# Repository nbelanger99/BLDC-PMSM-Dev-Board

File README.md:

### BLDC/PMSM Dev Board

This board wad designed to prototype control algorithms for BLDC/PMSM type motors. It features the typical 3-phase half-bridge architecture with discrete N-Channel Mosfets, and shunt resistors on two of the phases. It operates at an Arduino/RPi friendly 3.3v logic and breaks all signals out to a 0.1 inch header

With an Arduino or other platform, a battery/power supply, and a motor, this design could be used to start protoyping traditional 6-step commutation, or something more advanced like Field Oriented Control

<br>

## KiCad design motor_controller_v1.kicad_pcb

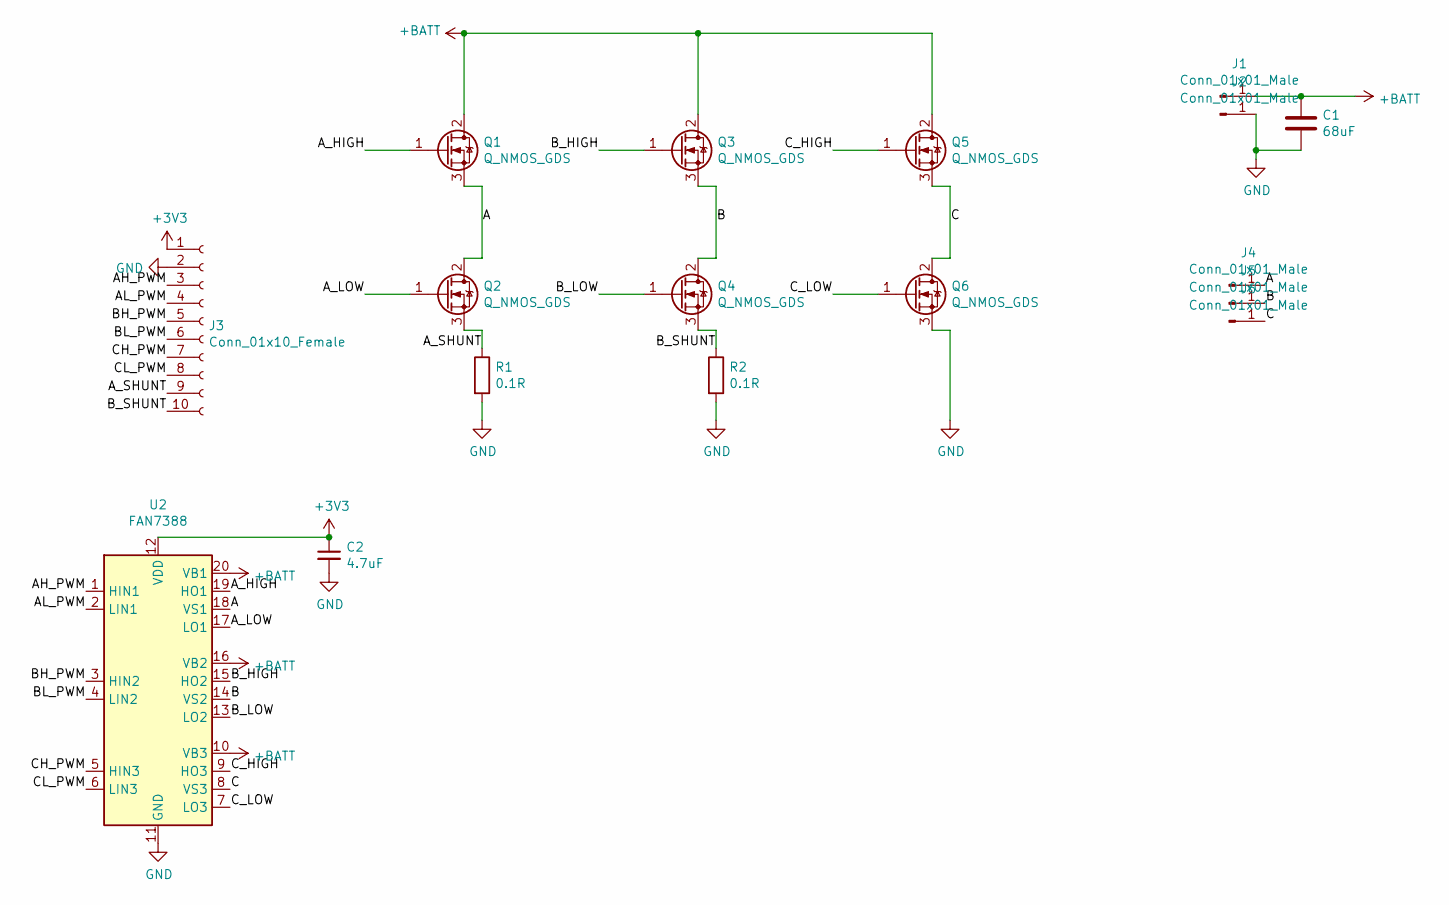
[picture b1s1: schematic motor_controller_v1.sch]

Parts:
C1: 68uF; CP_Radial_D18.0mm_P7.50mm
C2: 4.7uF; C_0603_1608Metric_Pad1.05x0.95mm_HandSolder
J1, J2, J4, J5, J6: Conn_01x01_Male; SolderWirePad_1x01_SMD_5x10mm
J3: Conn_01x10_Female; PinHeader_1x10_P2.54mm_Vertical
Q1, Q2, Q3, Q4, Q5, Q6: Q_NMOS_GDS; TO-220-3_Vertical
R1, R2: 0.1R; R_2512_6332Metric_Pad1.52x3.35mm_HandSolder
U2: FAN7388; SOIC-20W_7.5x12.8mm_P1.27mm

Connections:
+3V3: C2.1, J3.1, U2.12 (VDD)
+BATT: C1.1, J1.1, Q1.2 (D), Q3.2 (D), Q5.2 (D), U2.10 (VB3), U2.16 (VB2), U2.20 (VB1)
/A: J4.1, Q1.3 (S), Q2.2 (D), U2.18 (VS1)
/AH_PWM: J3.3, U2.1 (HIN1)
/AL_PWM: J3.4, U2.2 (LIN1)
/A_HIGH: Q1.1 (G), U2.19 (HO1)
/A_LOW: Q2.1 (G), U2.17 (LO1)
/A_SHUNT: J3.9, Q2.3 (S), R1.1
/B: J5.1, Q3.3 (S), Q4.2 (D), U2.14 (VS2)
/BH_PWM: J3.5, U2.3 (HIN2)
/BL_PWM: J3.6, U2.4 (LIN2)
/B_HIGH: Q3.1 (G), U2.15 (HO2)
/B_LOW: Q4.1 (G), U2.13 (LO2)
/B_SHUNT: J3.10, Q4.3 (S), R2.1
/C: J6.1, Q5.3 (S), Q6.2 (D), U2.8 (VS3)
/CH_PWM: J3.7, U2.5 (HIN3)
/CL_PWM: J3.8, U2.6 (LIN3)
/C_HIGH: Q5.1 (G), U2.9 (HO3)
/C_LOW: Q6.1 (G), U2.7 (LO3)
GND: C1.2, C2.2, J2.1, J3.2, Q6.3 (S), R1.2, R2.2, U2.11 (GND)

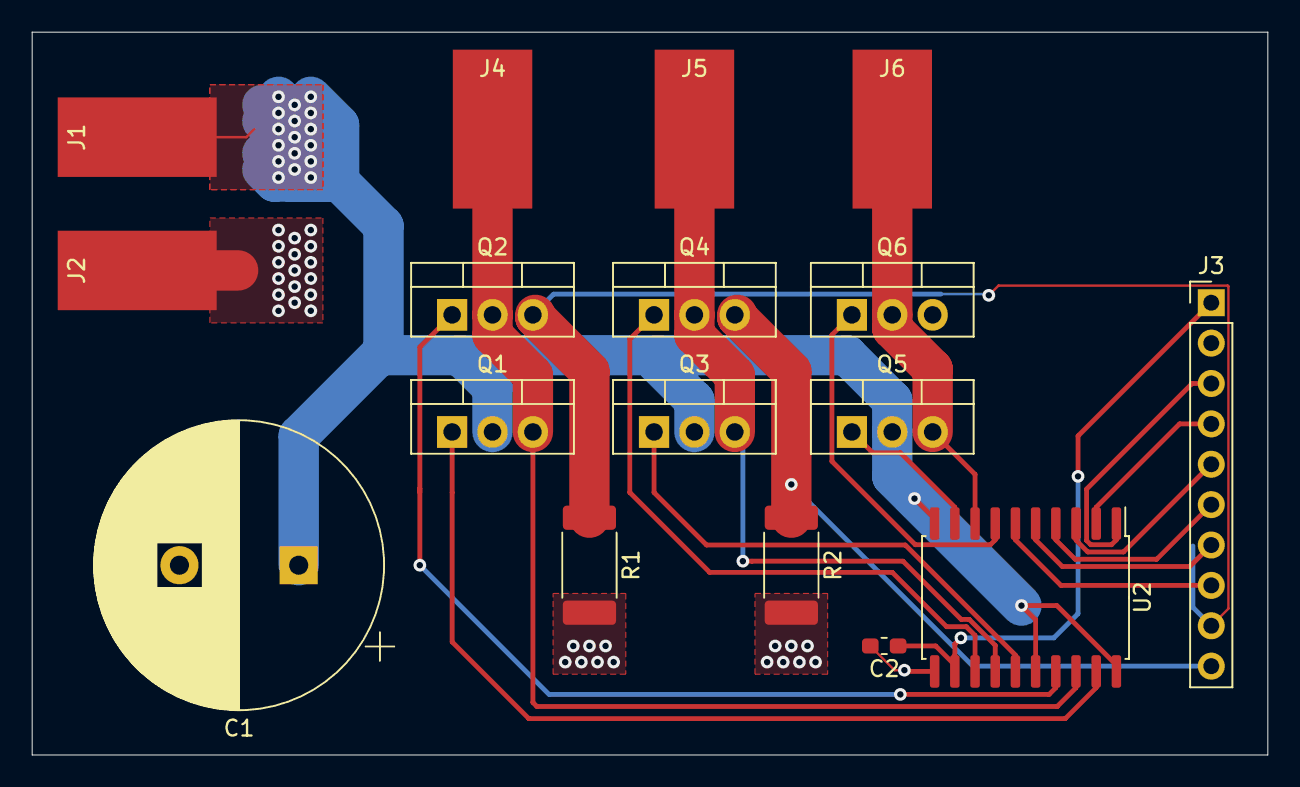
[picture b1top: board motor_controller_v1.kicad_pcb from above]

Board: 2 copper layers, 77.7 x 45.5 mm, 17 parts (0 on the bottom side), 20 nets.

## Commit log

2021-02-01 Initial design: no onboard ADC's
2021-02-10 Finishing layout
2021-02-10 Adding gitignore & readme
